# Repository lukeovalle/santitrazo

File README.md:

# Santitrazo
Seguidor de línea usando un atmega328p

## Estructura del directorio
placa/      proyecto de KiCAD
codigo/     código de Arduino
cuerpo/     piezas mecánicas (FreeCAD + STL)

## TODO
 - [ ] describir mejor el proyecto

## Mediciones 
Placa + sensores
    5V 0.9A
    
Motores
    5V  0.3A
    6V  1.3A

## Valores PID
Historial de pruebas. Los valores vigentes en el firmware están en las constantes
`k_prop`, `k_inte` y `k_dif` de `codigo/TaskController.cpp`.

P    | I      | D   | tiempo | pista grande
0.85 | 1e-3   | 6   | 4.6    |
0.9  | 2e-3   | 6   | 4.8    | 28
0.95 | 1.2e-3 | 6.2 | 5.2    |
0.85 | 1e-3   | 6   | --     | 27.88
0.92 | 1.2e-3 | 6.1 | 5.2    |
0.92 | 1.2e-3 | 6.1 | 4.7    | 28.3 (rigidizar ruedas traseras, lubricar placa, bat 7,1 V)
1    | 1.2e-3 | 6.2 | ------ |     (bat 7,8 V)
1.1  | 1.2e-3 | 6.8 | 5.7    |     (bat 7,8 V)
1    | 1.2e-3 | 3   | 4.6    |  (07/08/26 PID cada 10ms, promediado de sensores)
1.05 | 1.2e-3 | 5   | 4.6    | 
1.1  | 1.2e-3 | 6   | 4.4    |
1.1  | 1.5e-3 | 7   | 4.4    |
1.1  | 1.5e-3 | 8   | 4.4    | 24.3  (8.14V)

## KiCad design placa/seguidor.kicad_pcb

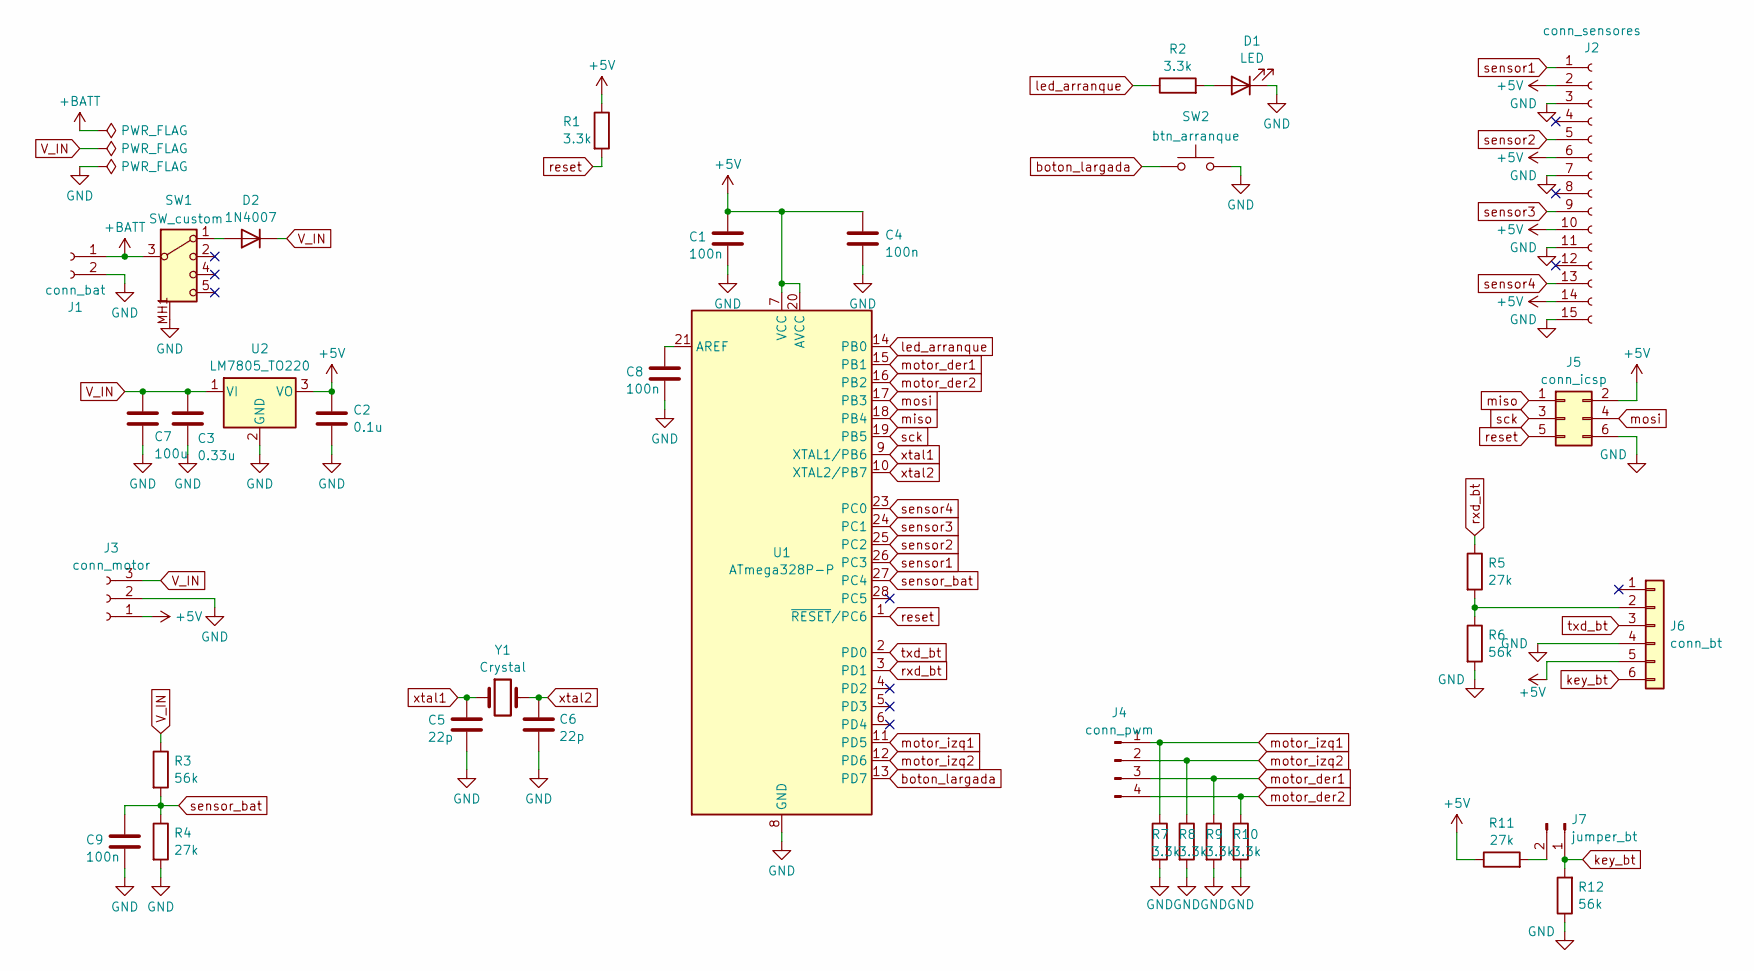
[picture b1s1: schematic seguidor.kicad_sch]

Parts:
C1, C4, C8, C9: 100n; C_Disc_D6.0mm_W2.5mm_P5.00mm
C2: 0.1u; CP_Radial_D5.0mm_P2.00mm
C3: 0.33u; CP_Radial_D5.0mm_P2.00mm
C5, C6: 22p; C_Disc_D4.7mm_W2.5mm_P5.00mm
C7: 100u; CP_Radial_D5.0mm_P2.00mm
D1: LED; LED_D4.0mm
D2: 1N4007; D_DO-41_SOD81_P10.16mm_Horizontal
J1: conn_bat; PinHeader_1x02_P2.54mm_Vertical
J2: conn_sensores; PinSocket_1x15_P2.54mm_Horizontal
J3: conn_motor; Molex_KK-254_AE-6410-03A_1x03_P2.54mm_Vertical
J4: conn_pwm; PinHeader_1x04_P2.54mm_Vertical
J5: conn_icsp; PinHeader_2x03_P2.54mm_Vertical
J6: conn_bt; PinSocket_1x06_P2.54mm_Vertical
J7: jumper_bt; PinHeader_1x02_P2.54mm_Vertical
R1, R2, R7, R8, R9, R10: 3.3k; R_Axial_DIN0204_L3.6mm_D1.6mm_P5.08mm_Horizontal
R3, R6, R12: 56k; R_Axial_DIN0204_L3.6mm_D1.6mm_P5.08mm_Horizontal
R4, R5, R11: 27k; R_Axial_DIN0207_L6.3mm_D2.5mm_P7.62mm_Horizontal
SW1: SW_custom; Switch custom
SW2: btn_arranque; SW_PUSH_6mm_H5mm
U1: ATmega328P-P; DIP-28_W7.62mm_Socket
U2: LM7805_TO220; TO-220-3_Vertical
Y1: Crystal; Crystal_HC49-4H_Vertical

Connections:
+5V: C1.1, C2.1, C4.1, J2.2, J2.6, J2.10, J2.14, J3.1, J5.2, J6.5, R1.1, R11.1, U1.7 (VCC), U1.20 (AVCC), U2.3 (VO)
+BATT: J1.1, SW1.3
GND: C1.2, C2.2, C3.2, C4.2, C5.2, C6.2, C7.2, C8.2, C9.2, D1.1 (K), J1.2, J2.3, J2.7, J2.11, J2.15, J3.2, J5.6, J6.4, R4.2, R6.2, R7.2, R8.2, R9.2, R10.2, R12.1, SW1.MH1 (CHASIS), SW1.MH2 (CHASIS), SW2.2, U1.8 (GND), U1.22 (GND), U2.2 (GND)
unnamed: D1.2 (A), R2.2
unnamed: D2.2 (A), SW1.1
unnamed: J6.2, R5.2, R6.1
unnamed: J7.2, R11.2
unnamed: C8.1, U1.21 (AREF)
V_IN: C3.1, C7.1, D2.1 (K), J3.3, R3.1, U2.1 (VI)
boton_largada: SW2.1, U1.13 (PD7)
key_bt: J6.6, J7.1, R12.2
led_arranque: R2.1, U1.14 (PB0)
miso: J5.1, U1.18 (PB4)
mosi: J5.4, U1.17 (PB3)
motor_der1: J4.3, R9.1, U1.15 (PB1)
motor_der2: J4.4, R10.1, U1.16 (PB2)
motor_izq1: J4.1, R7.1, U1.11 (PD5)
motor_izq2: J4.2, R8.1, U1.12 (PD6)
reset: J5.5, R1.2, U1.1 (~RESET/PC6)
rxd_bt: R5.1, U1.3 (PD1)
sck: J5.3, U1.19 (PB5)
sensor1: J2.1, U1.26 (PC3)
sensor2: J2.5, U1.25 (PC2)
sensor3: J2.9, U1.24 (PC1)
sensor4: J2.13, U1.23 (PC0)
sensor_bat: C9.1, R3.2, R4.1, U1.27 (PC4)
txd_bt: J6.3, U1.2 (PD0)
xtal1: C5.1, U1.9 (XTAL1/PB6), Y1.1
xtal2: C6.1, U1.10 (XTAL2/PB7), Y1.2

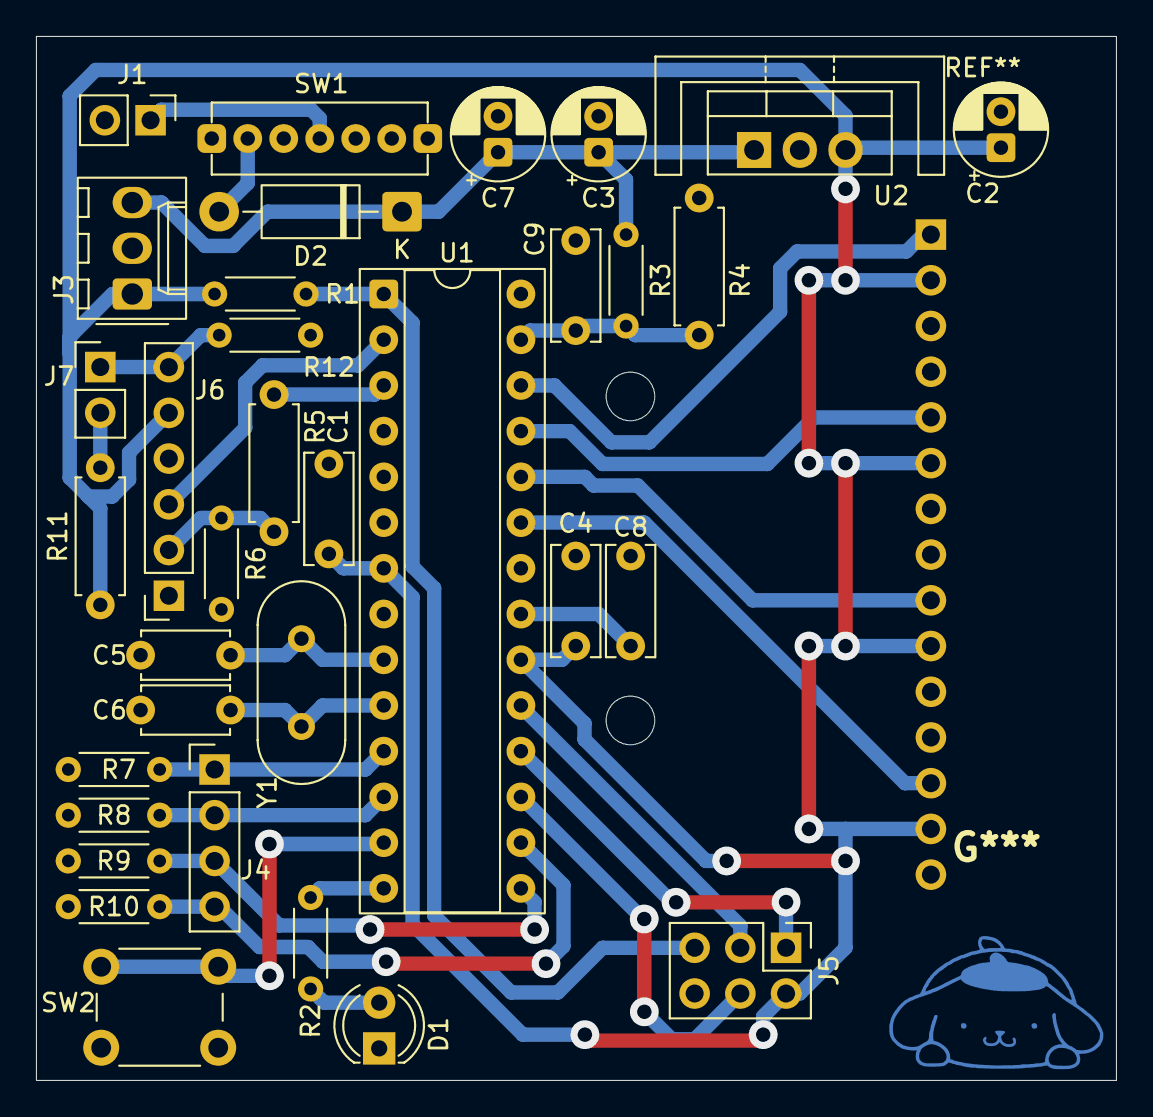
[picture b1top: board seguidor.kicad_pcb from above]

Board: 2 copper layers, 60.0 x 58.0 mm, 35 parts (1 on the bottom side), 29 nets.

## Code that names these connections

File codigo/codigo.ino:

#include "ClockMs.h"
#include "Executor.h"

#include "TaskLED.h"
#include "TaskBoton.h"
#include "TaskSensor.h"
#include "TaskMotor.h"
#include "TaskController.h"

#include "config.h"

ClockMs reloj; // contar ms entre llamados
Executor executor;

// Defino mis tareas
TaskLED led_arranque(10); // PB2
TaskBoton boton_largada(9); // PB1
TaskSensor sensor1(17); // PC3
TaskSensor sensor2(16); // PC2
TaskSensor sensor3(15); // PC1
TaskSensor sensor4(14); // PC0
// Motores: TaskMotor(pin PWM adelante, pin PWM atrás). ENA y ENB van siempre en
// alto (jumper puesto). Los cuatro pines tienen que tener PWM.
// Pines de la placa actual: los que ya tenían PWM (PD5 y PD6, pines 11 y 12 del
// DIP-28) quedan como "adelante"; los IN que antes iban a tierra pasan a PD3
// (pin 5) y PB3 (pin 17, compartido con MOSI del ICSP) como "atrás".
TaskMotor motor_izq(5, 3);  // adelante PD5 (pin 11), atrás PD3 (pin 5)
TaskMotor motor_der(6, 11); // adelante PD6 (pin 12), atrás PB3 (pin 17)


controller_contexto contexto = {
  .led_arranque = &led_arranque,
  .boton_largada = &boton_largada,
  .sensores = {&sensor1, &sensor2, &sensor3, &sensor4},
  .motor_izq = &motor_izq,
  .motor_der = &motor_der
};
TaskController controlador(&contexto, CONTROL_PERIODO_MS); // corre cada 10ms

void setup() {
  // Agrego las tareas al ejecutor
  executor.addTask(&led_arranque);
  executor.addTask(&boton_largada);
  executor.addTask(&sensor1);
  executor.addTask(&sensor2);
  executor.addTask(&sensor3);
  executor.addTask(&sensor4);
  executor.addTask(&motor_izq);
  executor.addTask(&motor_der);

  executor.addTask(&controlador);

  reloj.init();
  executor.init();
}

void loop() {
  unsigned long ticks = reloj.pending_ticks();
  executor.increaseTicks(ticks);

  executor.update();
}

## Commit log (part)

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2026-04-17 Circuito iniciado
2026-04-17 Create LICENSE
2026-04-17 Readme actualizado
2026-04-17 Código iniciado
2026-04-19 circuito modificado
2026-04-20 código para un LED
2026-04-20 ejecutor cíclico implementado a medias
2026-04-20 agregados componentes al pcb, faltan conectores
2026-04-23 cambiados capacitores en la placa
2026-05-09 Tamaño de la placa y agujeros
2026-05-11 Task LED en el código
2026-05-16 conector de 3 pines para el puente H
2026-05-29 placa editada
2026-06-11 Esqueleto del código, tareas definidas
2026-06-11 tareas botón y led implementadas
2026-06-12 tareas de motor y sensor implementadas
2026-06-12 tarea del controlador implementada
